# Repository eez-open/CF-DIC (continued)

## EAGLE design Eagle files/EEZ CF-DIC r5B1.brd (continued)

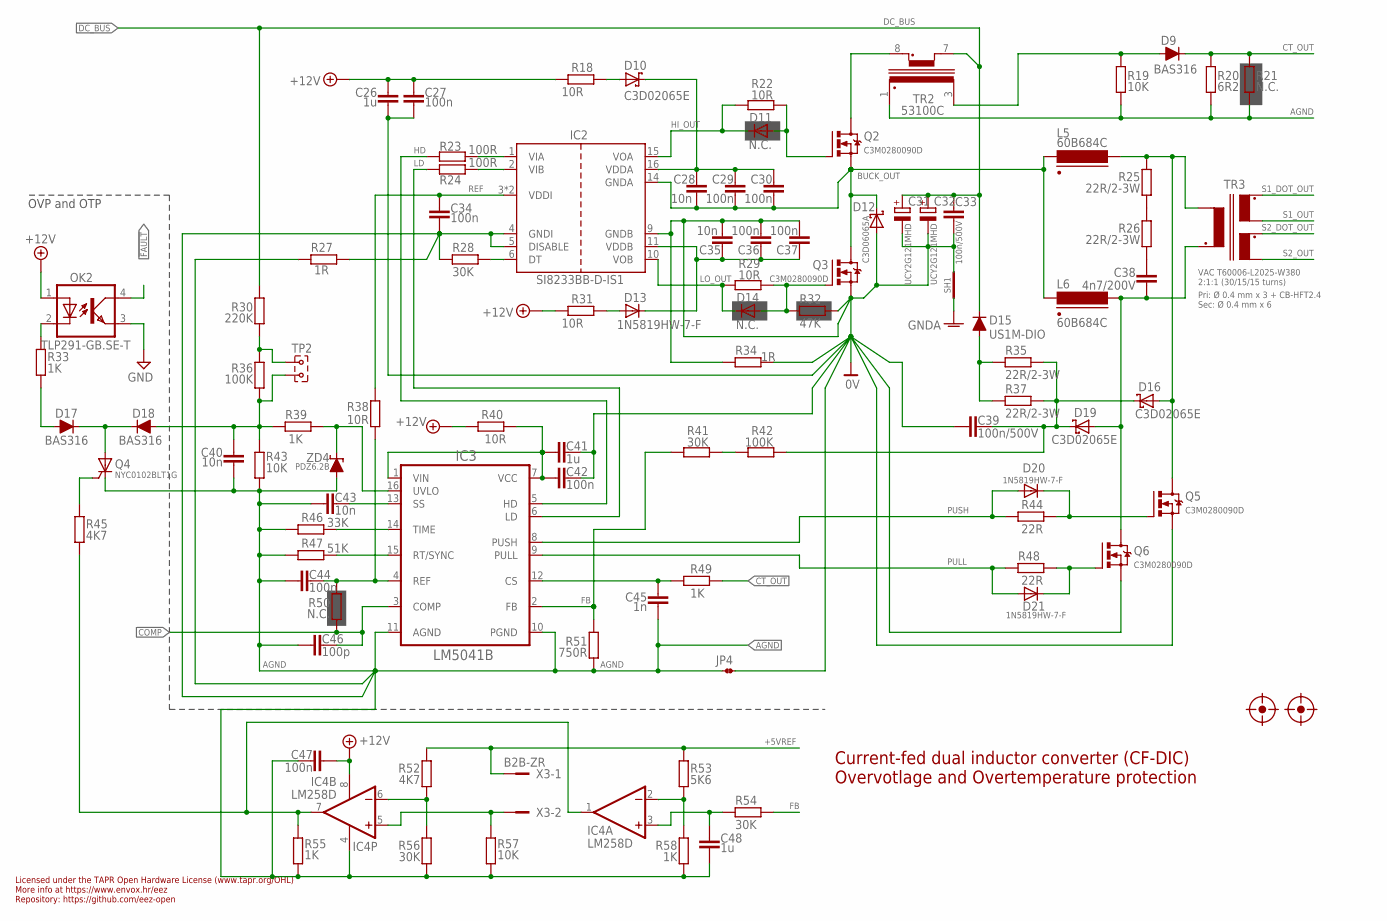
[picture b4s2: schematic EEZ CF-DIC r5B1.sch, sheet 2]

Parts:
C26, C41, C48: 1u; C0805
C27, C29, C30, C34, C36, C37, C42, C44, C47: 100n; C0603
C28, C35: 10n; C0603
C31, C32: UCY2G121MHD; ECAP7.5/18
C33, C39: 100n/500V; C1812
C38: 4n7/200V; C1210
C40, C43: 10n; C0805
C45: 1n; C0805
C46: 100p; C0805
D9, D17, D18: BAS316; SOD323-R
D10, D16, D19: C3D02065E; TO252
D11, D14: N.C.; SOD323-W
D12: C3D06065A; TO220-2
D13, D20, D21: 1N5819HW-7-F; SOD323-W
D15: US1M-DIO; DO214AA
FM1, FM2: FIDUCIAL_2; FIDUCIAL_DUAL
IC2: SI8233BB-D-IS1; SOIC-16
IC3: LM5041B; MTC16
IC4: LM258D; SOIC127P600X173-8N
JP4: JP2-NOCUT
L5, L6: 60B684C; MURATA_6000B
OK2: TLP291-GB.SE-T; SO4
Q2, Q3, Q5, Q6: C3M0280090D; TO247BV
Q4: NYC0102BLT1G; SOT23
R18, R22, R29, R31, R38, R40: 10R; R0805
R19, R43, R57: 10K; R0805
R20: 6R2; R0805
R21, R50: N.C.; R0805
R23, R24: 100R; R0805
R25, R26, R35, R37: 22R/2-3W; R2512
R27, R34: 1R; R0805
R28, R41, R54, R56: 30K; R0805
R30: 220K; R1206
R32: 47K; R0805
R33, R39, R49, R55, R58: 1K; R0805
R36, R42: 100K; R0805
R44, R48: 22R; R0805
R45, R52: 4K7; R0805
R46: 33K; R0805
R47: 51K; R0805
R51: 750R; R0805
R53: 5K6; R0805
SH1: SHORTNOHOLE; SHORT_NOHOLE
TP2: JUMPER-2PIN-2MM; 2MM-2
TR2: 53100C; MURATA_5300
TR3: VAC T60006-L2025-W380; VAC_DUAL_SEC
X3: B2B-ZR
ZD4: PDZ6.2B; SOD323-W

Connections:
0V: C26.1, C27.1, C31.-, C32.-, C33.2, C35.2, C36.2, C37.2, C39.1, C41.2, C42.2, D12.2 (A), IC2.9 (GNDB), JP4.2, Q3.S, Q5.S, Q6.S, R32.2, R34.1, R34.2, SH1.P$2 (GND_B); also elsewhere on the board
!FAULT: OK2.4 (COL); also elsewhere on the board
+5VREF: R52.2, R53.2, X3.1
+12V: C26.2, C27.2, C47.1, IC4.8 (V+), OK2.1 (A), R18.2, R31.2, R40.2; also elsewhere on the board
AGND: C34.1, C40.2, C43.1, C44.1, C45.1, C46.1, C47.2, C48.1, IC2.4 (GNDI), IC2.5 (DISABLE), IC3.10 (PGND), IC3.11 (AGND), IC4.4 (V-), JP4.1, Q4.1 (C), R19.2, R20.2, R21.2, R27.1, R27.2, R28.1, R43.2, R46.2, R47.2, R51.2, R55.2, R56.2, R57.2, R58.2, TR2.1 (S_DOT), ZD4.A; also elsewhere on the board
BUCK_OUT: C28.2, C29.2, C30.2, D12.1 (C), IC2.14 (GNDA), L5.2, L6.2, Q2.S, Q3.D
CLAMP_C: C39.2, D16.1 (C), D16.3 (C), D19.1 (C), D19.3 (C), R35.1, R37.1, R42.2
COMP: C46.2, IC3.3 (COMP), R50.2; also elsewhere on the board
CT_OUT: D9.C, R20.1, R21.1, R49.1
DC_BUS: C31.+, C32.+, C33.1, D15.C, R30.1, TR2.7; also elsewhere on the board
FB: IC3.2 (FB), R41.1, R51.1, R54.1
GND: OK2.3 (EMIT); also elsewhere on the board
GNDA: SH1.P$1 (GND_A); also elsewhere on the board
HD: IC3.5 (HD), R23.2
HI_OUT: D11.C, IC2.15 (VOA), R22.2
LD: IC3.6 (LD), R24.2
LO_OUT: D14.C, IC2.10 (VOB), R29.1
L_PULL: C38.2, D19.2 (A), L6.1, Q6.D, TR3.P1_DOT (P_DOT)
L_PUSH: D16.2 (A), L5.1, Q5.D, R25.2, TR3.P1
unnamed: R30.2, R36.1, TP2.1
unnamed: C28.1, C29.1, C30.1, D10.1 (C), D10.3 (C), IC2.16 (VDDA)
unnamed: R25.1, R26.2
unnamed: IC4.2 (-IN), R53.1, R58.1
unnamed: D20.C, Q5.G, R44.1
unnamed: D21.C, Q6.G, R48.1
unnamed: Q2.D, TR2.8 (P_DOT)
unnamed: C38.1, R26.1
unnamed: IC3.15 (RT/SYNC), R47.1
unnamed: D11.A, Q2.G, R22.1
unnamed: IC3.14 (TIME), R46.1
unnamed: C43.2, IC3.13 (SS)
unnamed: IC3.16 (UVLO), R39.1, ZD4.C
unnamed: IC4.6 (-IN), R52.1, R56.1
unnamed: D14.A, Q3.G, R29.2, R32.1
unnamed: R41.2, R42.1
unnamed: D10.2 (A), R18.1
unnamed: OK2.2 (C), R33.1
unnamed: C48.2, IC4.3 (+IN), R54.2
unnamed: D15.A, R35.2, R37.2
unnamed: IC2.1 (VIA), R23.1
unnamed: C45.2, IC3.12 (CS), R49.2
unnamed: IC4.1 (OUT), IC4.7 (OUT), R45.2, R55.1
unnamed: IC2.2 (VIB), R24.1
unnamed: IC4.5 (+IN), R57.1, X3.2
unnamed: IC2.6 (DT), R28.2
unnamed: D9.A, R19.1, TR2.3 (S)
unnamed: C41.1, C42.1, IC3.1 (VIN), IC3.7 (VCC), R40.1
unnamed: C35.1, C36.1, C37.1, D13.C, IC2.11 (VDDB)
unnamed: D13.A, R31.1
unnamed: C44.2, IC3.4 (REF), R38.1, R50.1
unnamed: Q4.2 (G), R45.1
unnamed: D17.C, D18.C, Q4.3 (A)
unnamed: D17.A, R33.2
PULL: D21.A, IC3.9 (PULL), R48.2
PUSH: D20.A, IC3.8 (PUSH), R44.2
REF: C34.2, IC2.3 (VDDI), IC2.8 (VDDI), R38.2
S1_DOT_OUT: TR3.S1_DOT; also elsewhere on the board
S1_OUT: TR3.S1; also elsewhere on the board
S2_DOT_OUT: TR3.S2_DOT; also elsewhere on the board
S2_OUT: TR3.S2; also elsewhere on the board
ULVO: C40.1, D18.A, R36.2, R39.2, R43.1, TP2.2

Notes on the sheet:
Licensed under the TAPR Open Hardware License (www.tapr.org/OHL)
Repository: https://github.com/eez-open
More info at https://www.envox.hr/eez
Current-fed dual inductor converter (CF-DIC) Overvotlage and Overtemperature protection
OVP and OTP
2:1:1 (30/15/15 turns)
Pri: Ø 0.4 mm x 3 + CB-HFT2.4
Sec: Ø 0.4 mm x 6

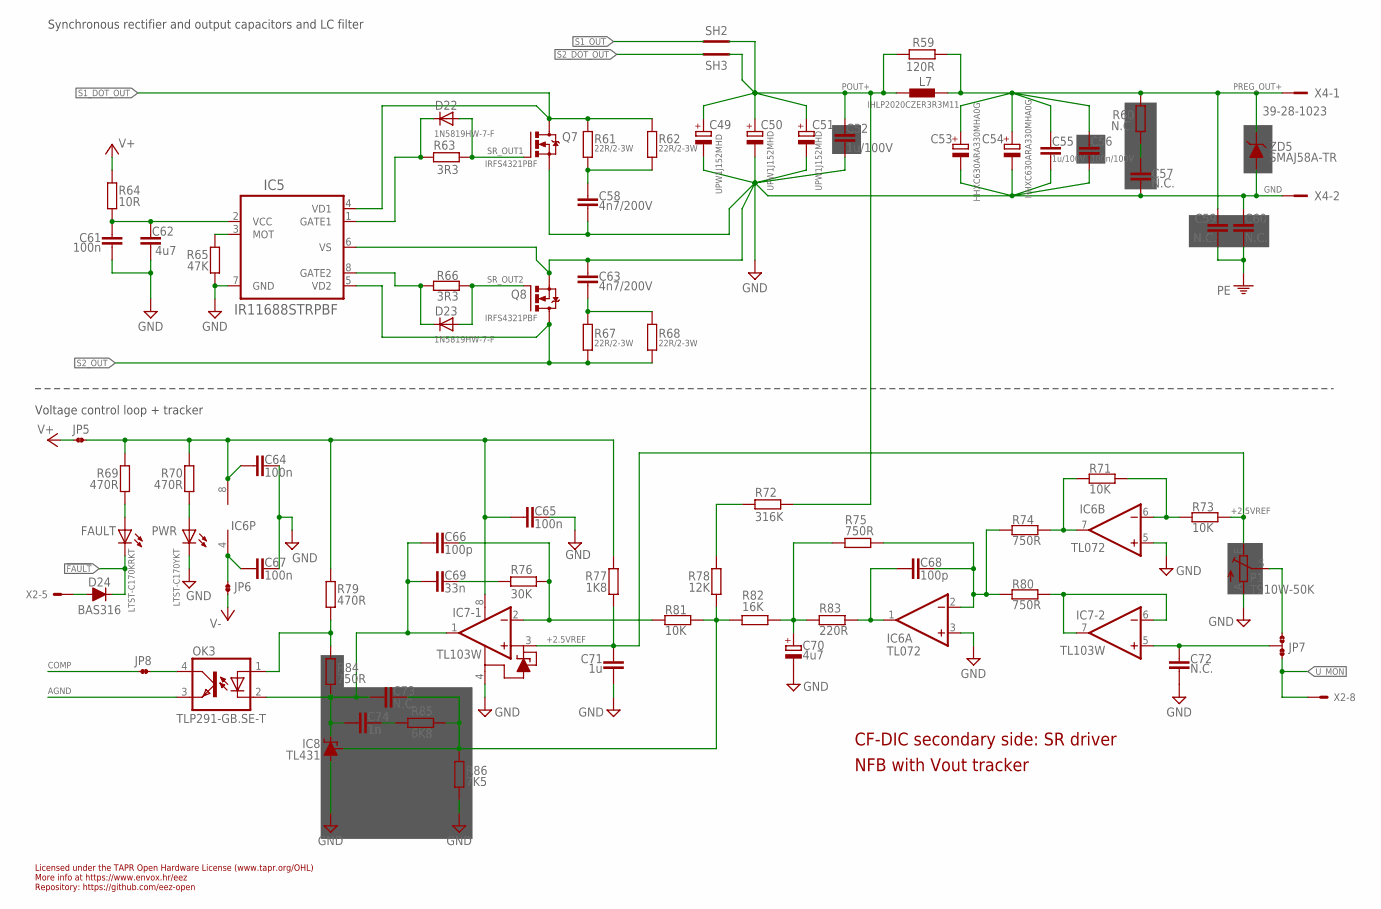
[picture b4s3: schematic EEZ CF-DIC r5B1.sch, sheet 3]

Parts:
C49, C50, C51: UPW1J152MHD; ECAP7.5/18
C52, C55: 1u/100V; C1206
C53: HHXC630ARA330MHA0G; CAPAE830X1050N; TOLERANCE ±20 %; VOLTAGERATING 63 V; MPN EEE-FK1J470P
C54: HHXC630ARA330MHA0G; CAPAE830X1050N
C56: 100n/100V; C1206
C57, C59, C60: N.C.; C1206
C58, C63: 4n7/200V; C1206
C61, C64, C65, C67: 100n; C0603
C62: 4u7; C1206
C66, C68: 100p; C0805
C69: 33n; C0805
C70: 4u7; EC1206
C71: 1u; C0805
C72, C73: N.C.; C0805
C74: 1n; C0805
D22, D23: 1N5819HW-7-F; SOD323-W
D24: BAS316; SOD323-R
FAULT: LTST-C170KRKT; LED_0805
IC5: IR11688STRPBF; SO8
IC6: TL072; SOIC127P600X173-8N
IC7: TL103W; SOIC127P600X173-8N
IC8: TL431; SOT103P240X110-3N
JP5, JP6, JP8: JP2-NOCUT
JP7: JP3-CUT
L7: IHLP2020CZER3R3M11; IHLP-2020BZ-11
OK3: TLP291-GB.SE-T; SO4
P1: T910W-50K; S64W
PWR: LTST-C170YKT; LED_0805
Q7, Q8: IRFS4321PBF; TO263
R59: 120R; R0805
R60: N.C.; R1210
R61, R62, R67, R68: 22R/2-3W; R2512
R63, R66: 3R3; R0805
R64: 10R; R0805
R65: 47K; R0805
R69, R70, R79: 470R; R0805
R71, R73, R81: 10K; R0805
R72: 316K; R0805
R74, R75, R80, R84: 750R; R0805
R76: 30K; R0805
R77: 1K8; R0805
R78: 12K; R0805
R82: 16K; R0805
R83: 220R; R0805
R85: 6K8; R0805
R86: 7K5; R0805
SH2, SH3: SHORTNOHOLE; SHORT_NOHOLE
X2: 90136-1208; 70543-08
X4: 39-28-1023; MINIFIT_5566-02A
ZD5: SMAJ58A-TR; DO214AC

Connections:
!FAULT: D24.C, FAULT.C; also elsewhere on the board
+2.5VREF: C71.1, IC7.3 (+IN1), P1.E, R73.2, R77.1
AGND: OK3.3 (EMIT); also elsewhere on the board
COMP: JP8.1; also elsewhere on the board
GND: C49.-, C50.-, C51.-, C52.2, C53.2, C54.2, C55.2, C56.2, C57.1, C58.2, C60.1, C61.2, C62.2, C63.2, C64.2, C65.2, C67.2, C70.-, C71.2, C72.2, IC5.6 (VS), IC5.7 (GND), IC6.3 (+IN), IC6.5 (+IN), IC7.4 (VCC-), IC8.3 (A), P1.A, PWR.C, Q7.2 (S), Q8.2 (S), R65.2, R86.1, X4.2, ZD5.A; also elsewhere on the board
unnamed: D24.A, X2.5
unnamed: C61.1, C62.1, IC5.2 (VCC), R64.2
unnamed: C57.2, R60.1
unnamed: C69.2, R76.2
unnamed: C66.2, IC7.2 (-IN1), R76.1, R81.1
unnamed: PWR.A, R70.2
unnamed: R72.1, R78.2
unnamed: FAULT.A, R69.2
unnamed: IC5.3 (MOT), R65.1
unnamed: C67.1, IC6.4 (V-), JP6.1
unnamed: JP8.2, OK3.4 (COL)
unnamed: C74.2, R85.1
unnamed: C64.1, C65.1, IC6.8 (V+), IC7.8 (VCC+), JP5.2, R69.1, R70.1, R77.2, R79.2
unnamed: IC6.7 (OUT), R71.1, R74.2
unnamed: C72.1, IC7.5 (+IN), JP7.COM
unnamed: JP7.NO, P1.S
unnamed: C68.2, IC6.2 (-IN), R74.1, R75.2, R80.1
unnamed: C58.1, R61.2, R62.2
unnamed: C63.1, R67.2, R68.2
unnamed: D22.C, IC5.1 (GATE1), R63.2
unnamed: D23.C, IC5.8 (GATE2), R66.2
unnamed: C66.1, C69.1, C73.1, C74.1, IC7.1 (OUT1), IC8.1 (C), OK3.2 (C), R84.2
unnamed: IC6.6 (-IN), R71.2, R73.1
unnamed: C68.1, IC6.1 (OUT), R83.2
NFB_IN: C73.2, IC8.2 (REF), R78.1, R81.2, R82.2, R85.2, R86.2
NFB_OFFSET: C70.+, R75.1, R82.1, R83.1
OK_A: OK3.1 (A), R79.1, R84.1
PE: C59.2, C60.2; also elsewhere on the board
POUT+: C49.+, C50.+, C51.+, C52.1, L7.1, R59.1, R72.2, SH2.P$2 (GND_B), SH3.P$1 (GND_A)
PREG_OUT+: C53.1, C54.1, C55.1, C56.1, C59.1, L7.2, R59.2, R60.2, X4.1, ZD5.C; also elsewhere on the board
S1_DOT_OUT: IC5.4 (VD1), Q7.3 (D), R61.1, R62.1; also elsewhere on the board
S1_OUT: SH2.P$1 (GND_A); also elsewhere on the board
S2_DOT_OUT: SH3.P$2 (GND_B); also elsewhere on the board
S2_OUT: IC5.5 (VD2), Q8.3 (D), R67.1, R68.1; also elsewhere on the board
SR_OUT1: D22.A, Q7.1 (G), R63.1
SR_OUT2: D23.A, Q8.1 (G), R66.1
U_MON: JP7.NC, X2.8
U_MON1: IC7.6 (-IN), IC7.7 (OUT), R80.2
V+: JP5.1, R64.1; also elsewhere on the board
V-: JP6.2; also elsewhere on the board

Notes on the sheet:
Licensed under the TAPR Open Hardware License (www.tapr.org/OHL)
Repository: https://github.com/eez-open
More info at https://www.envox.hr/eez
CF-DIC secondary side: SR driver
NFB with Vout tracker
Voltage control loop + tracker
Synchronous rectifier and output capacitors and LC filter

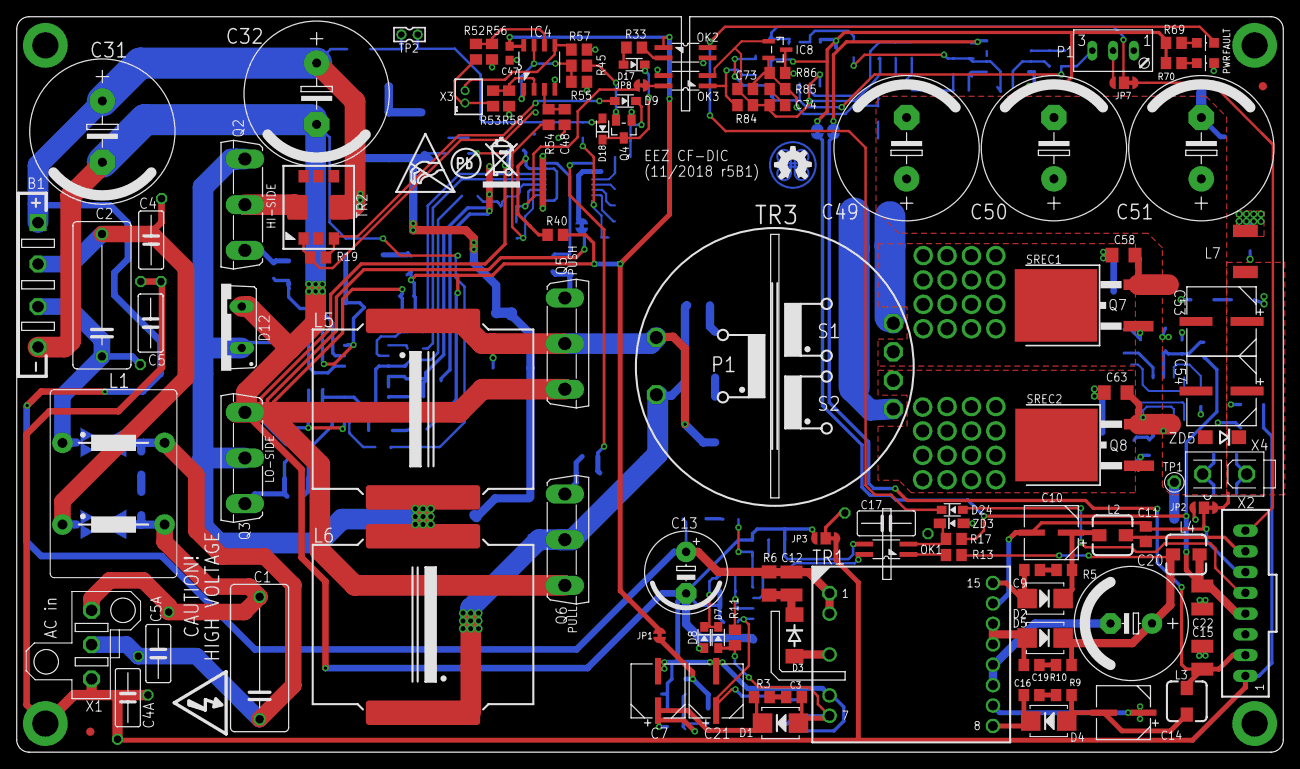
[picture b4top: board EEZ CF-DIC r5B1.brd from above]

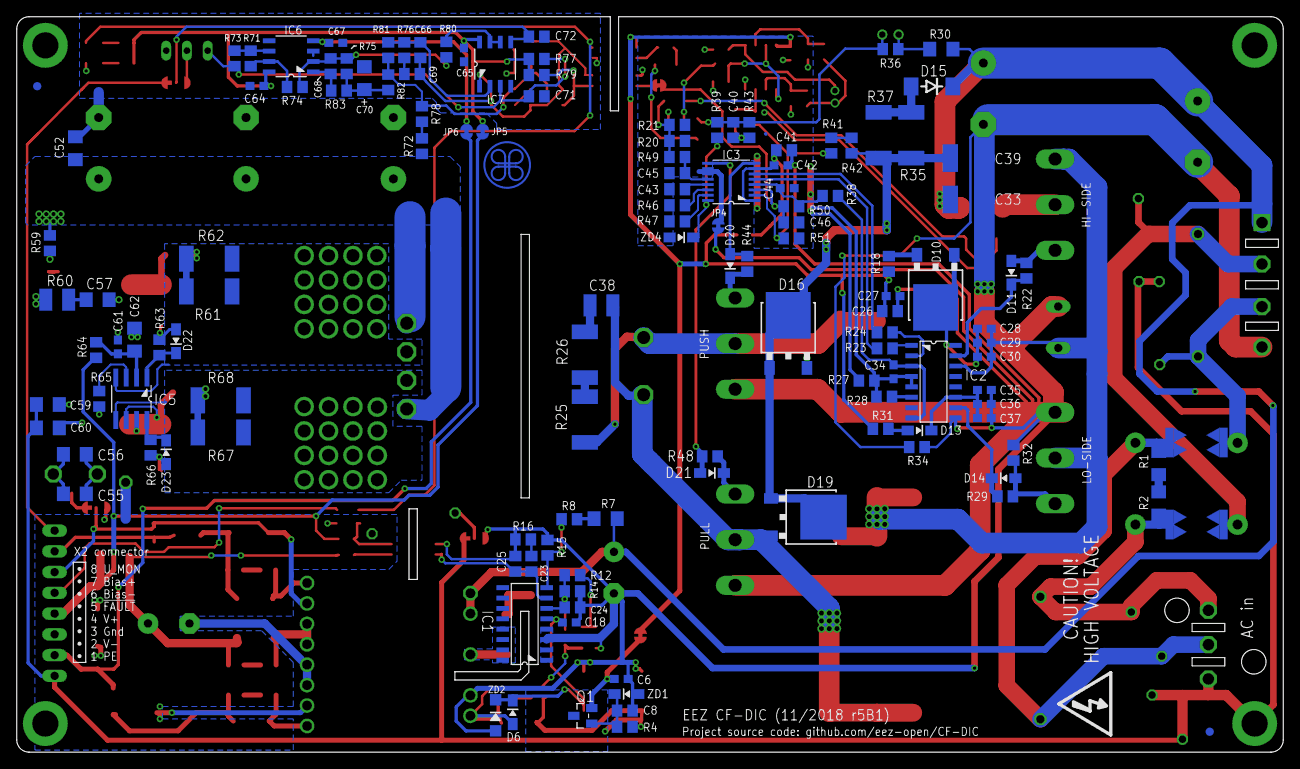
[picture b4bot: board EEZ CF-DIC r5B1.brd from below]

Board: 2 copper layers, 155.0 x 90.0 mm, 249 parts (132 on the bottom side), 131 nets.

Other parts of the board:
EEZ_SIGNATURE: SIGNATURESMALL; SIGNATURE_5MM
U$2: RECYCLE_BIN1/8
U$4: ESD_SYMBOL
U$5: PB_SMALL

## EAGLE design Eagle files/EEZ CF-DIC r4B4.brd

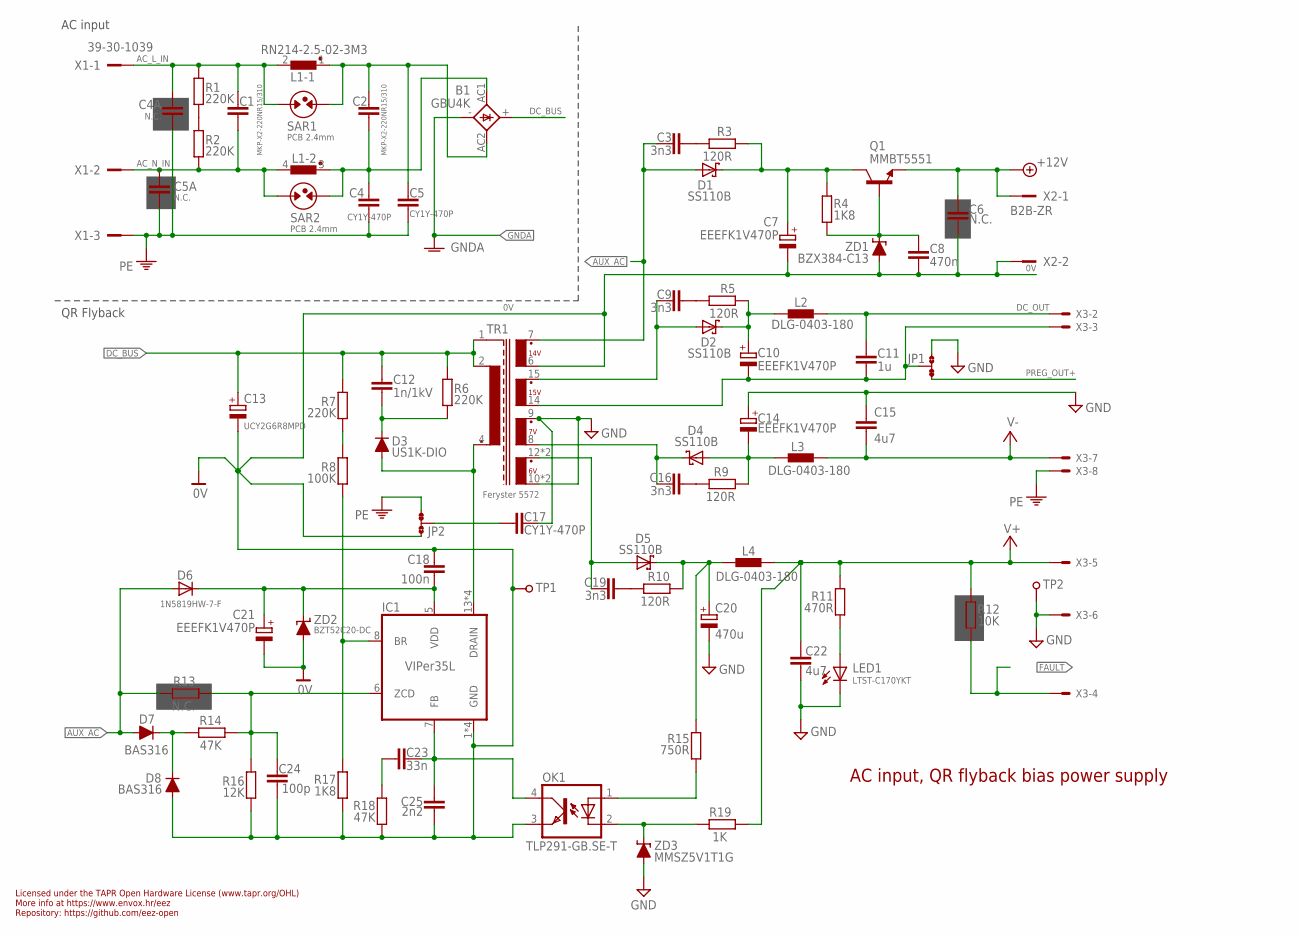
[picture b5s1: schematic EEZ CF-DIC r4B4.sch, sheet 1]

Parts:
B1: GBU4K; GBU4K_CRE
C1, C2: MKP-X2-220NR15/310; C150-072X183
C3, C9, C16, C19: 3n3; C0805
C4, C5, C17: CY1Y-470P; CY075-032X103
C4A, C5A: N.C.; CY075-032X103
C6: N.C.; C0603
C7, C10, C14, C21: EEEFK1V470P; CAPAE660X610N
C8: 470n; C0805
C11: 1u; C0805
C12: 1n/1kV; C1210
C13: UCY2G6R8MPD; ECAP5/10.5
C15, C22: 4u7; C1206
C18: 100n; C0603
C20: 470u; ECAP5/10.5
C23: 33n; C0805
C24: 100p; C0805
C25: 2n2; C0805
D1, D2, D4, D5: SS110B; SMB
D3: US1K-DIO; DO214AA
D6: 1N5819HW-7-F; SOD323-W
D7, D8: BAS316; SOD323-R
IC1: VIPer35L; SOIC-16
JP1, JP2: JP3-CUT
L1: RN214-2.5-02-3M3; RN214; FARNELL 1191518
L2, L3, L4: DLG-0403-180; DE0403
LED1: LTST-C170YKT; LED_0805
OK1: TLP291-GB.SE-T; SO4
Q1: MMBT5551; SOT23-BEC
R1, R2, R6, R7: 220K; R1206
R3, R5, R9, R10: 120R; R0805
R4, R17: 1K8; R0805
R8: 100K; R0805
R11: 470R; R0805
R12: 10K; R0805
R13: N.C.; R0805
R14, R18: 47K; R0805
R15: 750R; R0805
R16: 12K; R0805
R19: 1K; R0805
SAR1, SAR2: PCB 2.4mm; PCB-SAR_2.4MM
TP1, TP2: PCB_TEST_TABSHIELD; PCB_SHIELD_TAB
TR1: Feryster 5572; FERYSTER_5572
X1: 39-30-1039; MINIFIT_39301039_CRE
X2: B2B-ZR
X3: 90136-1208; 70543-08
ZD1: BZX384-C13; SOD323-W
ZD2: BZT52C20-DC; SOD123
ZD3: MMSZ5V1T1G; SOD323-W

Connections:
0V: C6.2, C7.2 (-), C8.2, C13.-, C18.1, C21.2 (-), C24.2, C25.2, D8.A, IC1.1 (GND), IC1.2 (GND), IC1.3 (GND), IC1.4 (GND), JP2.NO, OK1.3 (EMIT), R16.1, R17.2, R18.2, TP1.1, TR1.6 (S_BIAS), X2.2, ZD1.A, ZD2.A; also elsewhere on the board
6VAC: C19.2, D5.A, TR1.12 (S1_DOT), TR1.13 (S1_DOT)
7VAC: C16.2, D4.C, TR1.8 (S2)
15VAC: C9.2, D2.A, TR1.15 (S3_DOT)
!FAULT: R12.2, X3.4; also elsewhere on the board
+6V_REC: C20.+, D5.C, L4.1, R10.1, R15.1
+12V: C6.1, Q1.E, X2.1; also elsewhere on the board
+15V_REC: C10.1 (+), D2.C, L2.1, R5.1
-7V_REC: C14.2 (-), D4.A, L3.1, R9.1
-15V: C10.2 (-), C11.2, JP1.COM, TR1.14 (S3), X3.3
AC_L_IN: C1.1, C4A.2, L1.2, R1.1, SAR1.1, X1.1
AC_N_IN: C1.2, C5A.2, L1.4 (2), R2.2, SAR2.1, X1.2
AUX_AC: C3.2, D1.A, D6.A, D7.A, R13.2, TR1.7 (S_BIAS_DOT)
AUX_REC: C7.1 (+), D1.C, Q1.C, R3.1, R4.1
DC_BUS: B1.+, C12.1, C13.+, R6.1, R7.1, TR1.1 (SHIELD), TR1.2; also elsewhere on the board
DC_OUT: C11.1, L2.2, X3.2
FB2: OK1.2 (C), R19.1, ZD3.C
GND: C14.1 (+), C15.1, C17.2, C20.-, C22.2, JP1.NO, LED1.C, TP2.1, TR1.9 (S2_DOT), TR1.10 (S1), TR1.11 (S1), X3.6, ZD3.A; also elsewhere on the board
GNDA: B1.-; also elsewhere on the board
unnamed: C17.1, JP2.COM
unnamed: LED1.A, R11.2
unnamed: B1.AC2, C2.1, C5.2, L1.1, SAR1.2
unnamed: IC1.8 (BR), R8.2, R17.1
unnamed: B1.AC1, C2.2, C4.2, L1.3 (1), SAR2.2
unnamed: C18.2, C21.1 (+), D6.C, IC1.5 (VDD), ZD2.C
unnamed: R1.2, R2.1
unnamed: R7.2, R8.1
unnamed: C8.1, Q1.B, R4.2, ZD1.C
unnamed: OK1.1 (A), R15.2
unnamed: C12.2, D3.C, R6.2
unnamed: C23.2, C25.1, IC1.7 (FB), OK1.4 (COL)
unnamed: C9.1, R5.2
unnamed: C3.1, R3.2
unnamed: C24.1, IC1.6 (ZCD), R13.1, R14.1, R16.2
unnamed: C16.1, R9.2
unnamed: C19.1, R10.2
unnamed: C23.1, R18.1
unnamed: D7.C, D8.C, R14.2
PE: C4.1, C4A.1, C5.1, C5A.1, JP2.NC, X1.3, X3.8
PREG_OUT+: JP1.NC; also elsewhere on the board
V+: C22.1, L4.2, R11.1, R12.1, R19.2, X3.5; also elsewhere on the board
V-: C15.2, L3.2, X3.7; also elsewhere on the board
VIPER_D: D3.A, IC1.13 (DRAIN), IC1.14 (DRAIN), IC1.15 (DRAIN), IC1.16 (DRAIN), TR1.4 (P2_DOT)

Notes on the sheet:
Licensed under the TAPR Open Hardware License (www.tapr.org/OHL)
Repository: https://github.com/eez-open
More info at https://www.envox.hr/eez
AC input, QR flyback bias power supply
QR Flyback
AC input

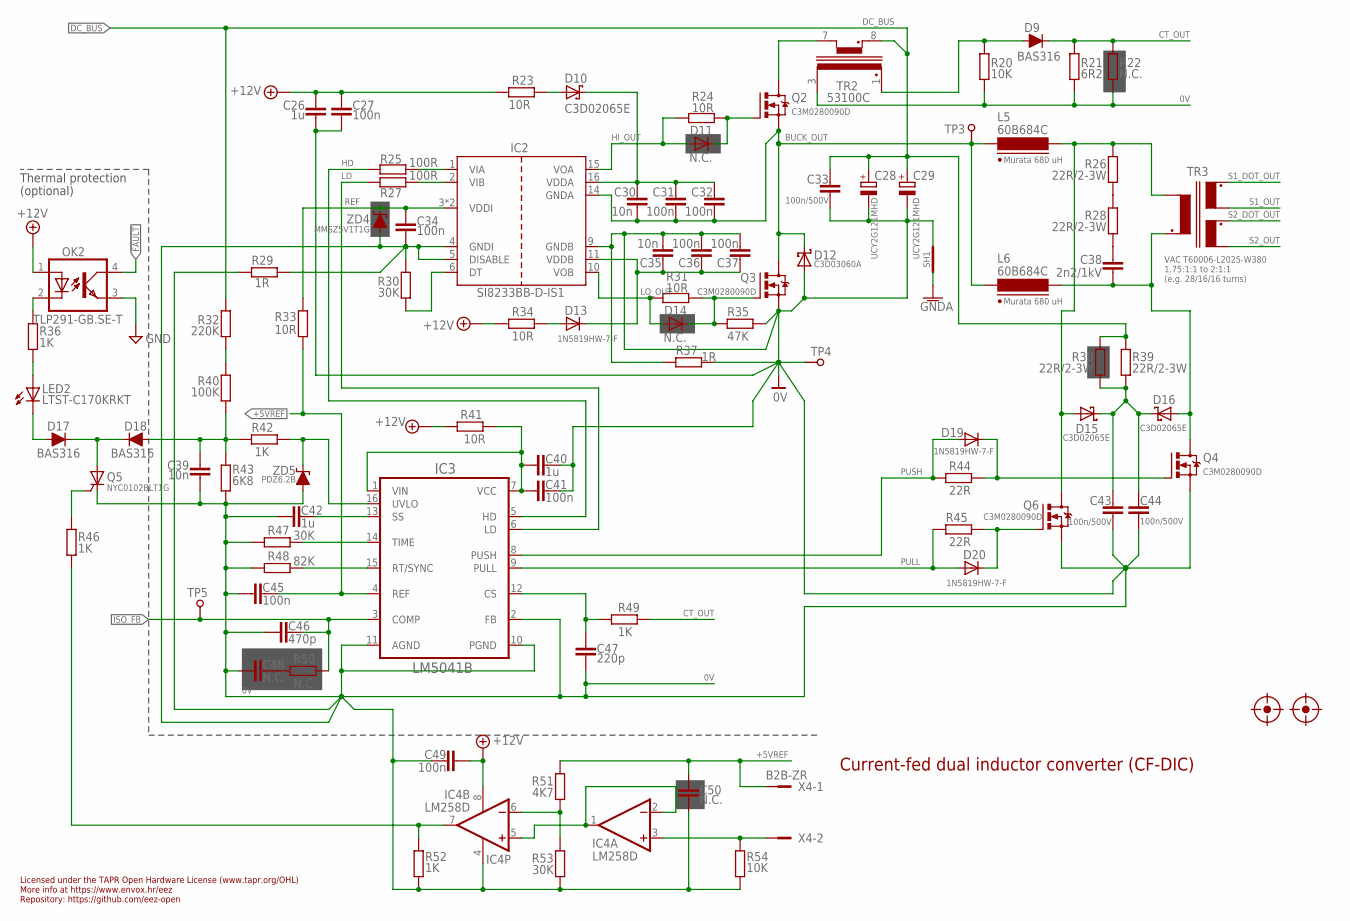
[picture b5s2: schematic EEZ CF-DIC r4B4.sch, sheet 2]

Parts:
C26, C40, C42: 1u; C0805
C27, C31, C32, C34, C36, C37, C41, C45, C49: 100n; C0603
C28, C29: UCY2G121MHD; ECAP7.5/18
C30, C35, C39: 10n; C0603
C33, C43, C44: 100n/500V; C1812
C38: 2n2/1kV; C1210
C46: 470p; C0805
C47: 220p; C0805
C48: N.C.; C0805
C50: N.C.; C0603
D9, D17, D18: BAS316; SOD323-R
D10, D15, D16: C3D02065E; TO252
D11, D14: N.C.; SOD323-W
D12: C3D03060A; TO220-2
D13, D19, D20: 1N5819HW-7-F; SOD323-W
FM1, FM2: FIDUCIAL_2; FIDUCIAL_DUAL
IC2: SI8233BB-D-IS1; SOIC-16
IC3: LM5041B; MTC16
IC4: LM258D; SOIC127P600X173-8N
L5, L6: 60B684C; MURATA_6000B
LED2: LTST-C170KRKT; LED_0805
OK2: TLP291-GB.SE-T; SO4
Q2, Q3, Q4, Q6: C3M0280090D; TO247BV-ROUND
Q5: NYC0102BLT1G; SOT23
R20, R54: 10K; R0805
R21: 6R2; R0805
R22, R50: N.C.; R0805
R23, R24, R31, R33, R34, R41: 10R; R0805
R25, R27: 100R; R0805
R26, R28, R38, R39: 22R/2-3W; R2512
R29, R37: 1R; R0805
R30, R47, R53: 30K; R0805
R32: 220K; R1206
R35: 47K; R0805
R36, R42, R46, R49, R52: 1K; R0805
R40: 100K; R0805
R43: 6K8; R0805
R44, R45: 22R; R0805
R48: 82K; R0805
R51: 4K7; R0805
SH1: SHORTNOHOLE; SHORT_NOHOLE
TP3, TP4, TP5: PCB_TEST_TABSHIELD; PCB_SHIELD_TAB
TR2: 53100C; MURATA_5300
TR3: VAC T60006-L2025-W380; VAC_DUAL_SEC
X4: B2B-ZR
ZD4: MMSZ5V1T1G; SOD323-W
ZD5: PDZ6.2B; SOD323-W

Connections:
0V: C26.1, C27.1, C28.-, C29.-, C33.1, C34.1, C35.2, C36.2, C37.2, C39.2, C40.2, C41.2, C42.1, C43.1, C44.1, C45.1, C46.1, C47.1, C48.1, C49.2, C50.2, D12.2 (A), IC2.4 (GNDI), IC2.5 (DISABLE), IC2.9 (GNDB), IC3.2 (FB), IC3.10 (PGND), IC3.11 (AGND), IC4.4 (V-), Q3.S, Q4.S, Q5.1 (C), Q6.S, R20.2, R21.2, R22.2, R29.1, R29.2, R30.1, R35.2, R37.1, R37.2, R43.2, R47.2, R48.2, R52.2, R53.2, R54.2, SH1.P$2 (GND_B), TP4.1, TR2.3 (S), ZD4.A, ZD5.A; also elsewhere on the board
!FAULT: OK2.4 (COL); also elsewhere on the board
+5VREF: C45.2, C50.1, IC3.4 (REF), R33.1, R51.2, X4.1
+12V: C26.2, C27.2, C49.1, IC4.8 (V+), OK2.1 (A), R23.2, R34.2, R41.2; also elsewhere on the board
BUCK_OUT: C30.2, C31.2, C32.2, D12.1 (C), IC2.14 (GNDA), L5.2, L6.2, Q2.S, Q3.D, TP3.1
CLAMP_C: C43.2, C44.2, D15.1 (C), D15.3 (C), D16.1 (C), D16.3 (C), R38.1, R39.1
CT_OUT: D9.C, R21.1, R22.1, R49.1
DC_BUS: C28.+, C29.+, C33.2, R32.1, R38.2, R39.2, TR2.8 (P_DOT); also elsewhere on the board
GND: OK2.3 (EMIT); also elsewhere on the board
GNDA: SH1.P$1 (GND_A); also elsewhere on the board
HD: IC3.5 (HD), R25.2
HI_OUT: D11.A, IC2.15 (VOA), R24.2
ISO_FB: C46.2, IC3.3 (COMP), R50.1, TP5.1; also elsewhere on the board
LD: IC3.6 (LD), R27.2
LO_OUT: D14.A, IC2.10 (VOB), R31.1
L_PULL: D15.2 (A), L5.1, Q6.D, R26.2, TR3.P1
L_PUSH: C38.2, D16.2 (A), L6.1, Q4.D, TR3.P1_DOT (P_DOT)
unnamed: R32.2, R40.1
unnamed: C30.1, C31.1, C32.1, D10.1 (C), D10.3 (C), IC2.16 (VDDA)
unnamed: R26.1, R28.2
unnamed: IC4.3 (+IN), R54.1, X4.2
unnamed: D19.C, Q4.G, R44.1
unnamed: D20.C, Q6.G, R45.1
unnamed: LED2.A, R36.2
unnamed: C38.1, R28.1
unnamed: IC3.15 (RT/SYNC), R48.1
unnamed: D11.C, Q2.G, R24.1
unnamed: IC3.14 (TIME), R47.1
unnamed: C42.2, IC3.13 (SS)
unnamed: IC3.16 (UVLO), R42.1, ZD5.C
unnamed: IC4.6 (-IN), R51.1, R53.1
unnamed: D14.C, Q3.G, R31.2, R35.1
unnamed: D10.2 (A), R23.1
unnamed: OK2.2 (C), R36.1
unnamed: C48.2, R50.2
unnamed: IC2.1 (VIA), R25.1
unnamed: C47.2, IC3.12 (CS), R49.2
unnamed: IC4.7 (OUT), R46.2, R52.1
unnamed: IC2.2 (VIB), R27.1
unnamed: IC4.1 (OUT), IC4.2 (-IN), IC4.5 (+IN)
unnamed: IC2.6 (DT), R30.2
unnamed: D9.A, R20.1, TR2.1 (S_DOT)
unnamed: C40.1, C41.1, IC3.1 (VIN), IC3.7 (VCC), R41.1
unnamed: C35.1, C36.1, C37.1, D13.C, IC2.11 (VDDB)
unnamed: Q2.D, TR2.7
unnamed: D13.A, R34.1
unnamed: Q5.2 (G), R46.1
unnamed: D17.C, D18.C, Q5.3 (A)
unnamed: D17.A, LED2.C
PULL: D20.A, IC3.9 (PULL), R45.2
PUSH: D19.A, IC3.8 (PUSH), R44.2
REF: C34.2, IC2.3 (VDDI), IC2.8 (VDDI), R33.2, ZD4.C
S1_DOT_OUT: TR3.S1_DOT; also elsewhere on the board
S1_OUT: TR3.S1; also elsewhere on the board
S2_DOT_OUT: TR3.S2_DOT; also elsewhere on the board
S2_OUT: TR3.S2; also elsewhere on the board
ULVO: C39.1, D18.A, R40.2, R42.2, R43.1

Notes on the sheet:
Licensed under the TAPR Open Hardware License (www.tapr.org/OHL)
Repository: https://github.com/eez-open
More info at https://www.envox.hr/eez
Current-fed dual inductor converter (CF-DIC)
1.75:1:1 to 2:1:1
Murata 680 uH
(e.g. 28/16/16 turns)
(optional)
Thermal protection

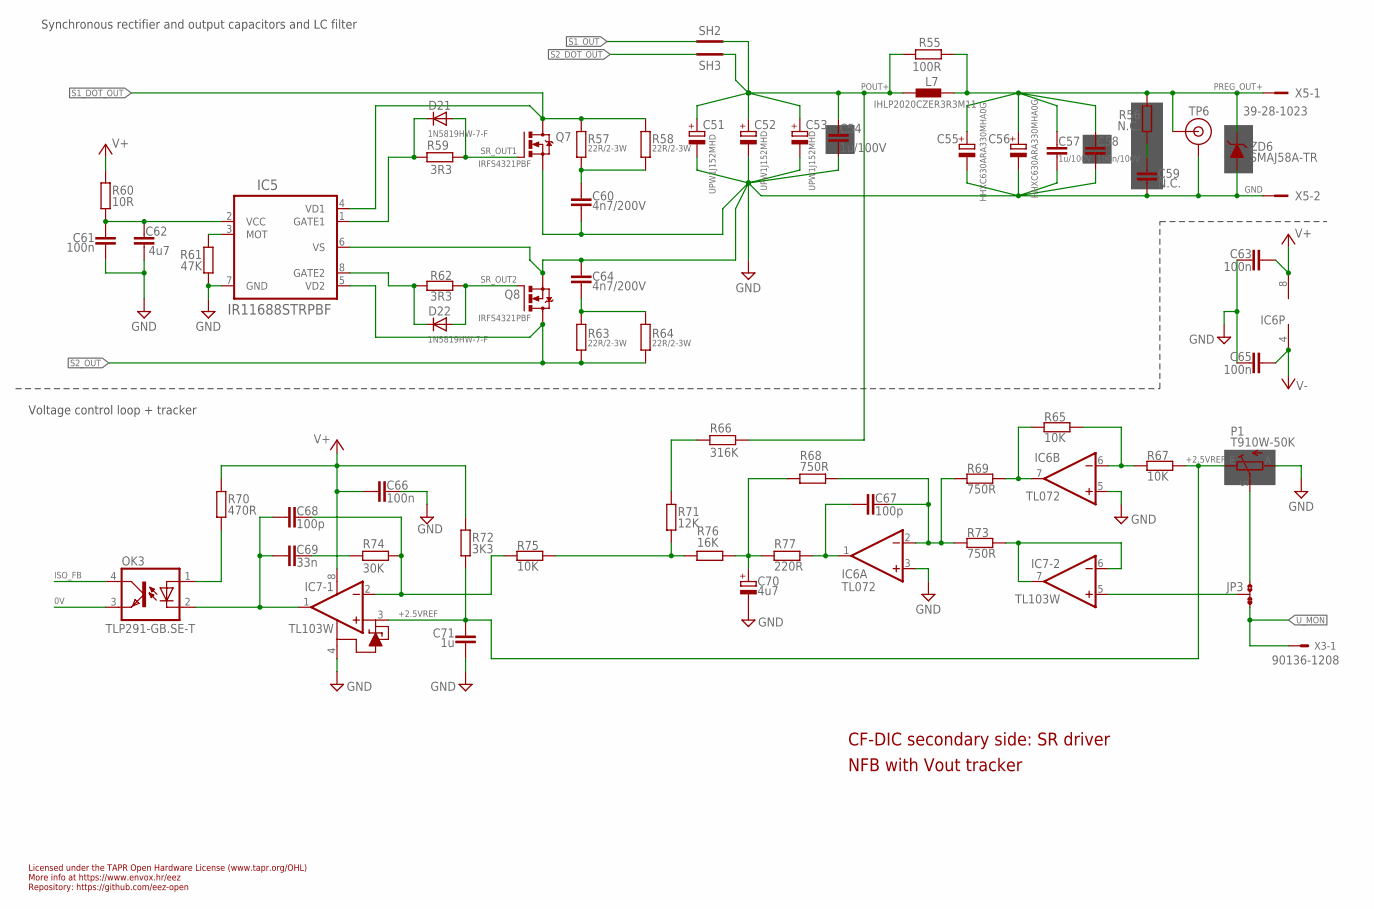
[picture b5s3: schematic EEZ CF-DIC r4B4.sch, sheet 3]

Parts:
C51, C52, C53: UPW1J152MHD; ECAP7.5/18
C54, C57: 1u/100V; C1206
C55: HHXC630ARA330MHA0G; CAPAE830X1050N; TOLERANCE ±20 %; VOLTAGERATING 63 V; MPN EEE-FK1J470P
C56: HHXC630ARA330MHA0G; CAPAE830X1050N
C58: 100n/100V; C0805
C59: N.C.; C1206
C60, C64: 4n7/200V; C1206
C61, C63, C65, C66: 100n; C0603
C62: 4u7; C1206
C67, C68: 100p; C0805
C69: 33n; C0805
C70: 4u7; EC1206
C71: 1u; C0805
D21, D22: 1N5819HW-7-F; SOD323-W
IC5: IR11688STRPBF; SO8
IC6: TL072; SOIC127P600X173-8N
IC7: TL103W; SOIC127P600X173-8N
JP3: JP3-CUT
L7: IHLP2020CZER3R3M11; IHLP-2020BZ-11
OK3: TLP291-GB.SE-T; SO4
P1: T910W-50K; S64W
Q7, Q8: IRFS4321PBF; TO263
R55: 100R; R0805
R56: N.C.; R1210
R57, R58, R63, R64: 22R/2-3W; R2512
R59, R62: 3R3; R0805
R60: 10R; R0805
R61: 47K; R0805
R65, R67, R75: 10K; R0805
R66: 316K; R0805
R68, R69, R73: 750R; R0805
R70: 470R; R0805
R71: 12K; R0805
R72: 3K3; R0805
R74: 30K; R0805
R76: 16K; R0805
R77: 220R; R0805
SH2, SH3: SHORTNOHOLE; SHORT_NOHOLE
TP6: TEST_POINT-2; TP_1.1MM_2
X3: 90136-1208; 70543-08
X5: 39-28-1023; MINIFIT_5566-02A
ZD6: SMAJ58A-TR; DO214AC

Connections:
0V: OK3.3 (EMIT); also elsewhere on the board
+2.5VREF: C71.1, IC7.3 (+IN1), P1.E, R67.2, R72.1
FB: R71.1, R75.2, R76.2
GND: C51.-, C52.-, C53.-, C54.2, C55.2, C56.2, C57.2, C58.2, C59.1, C60.2, C61.2, C62.2, C63.2, C64.2, C65.2, C66.2, C70.-, C71.2, IC5.6 (VS), IC5.7 (GND), IC6.3 (+IN), IC6.5 (+IN), IC7.4 (VCC-), P1.A, Q7.2 (S), Q8.2 (S), R61.2, TP6.GND, X5.2, ZD6.A; also elsewhere on the board
ISO_FB: OK3.4 (COL); also elsewhere on the board
unnamed: C61.1, C62.1, IC5.2 (VCC), R60.2
unnamed: C59.2, R56.1
unnamed: C69.2, R74.2
unnamed: C68.2, IC7.2 (-IN1), R74.1, R75.1
unnamed: R66.1, R71.2
unnamed: IC5.3 (MOT), R61.1
unnamed: IC6.7 (OUT), R65.1, R69.2
unnamed: IC7.5 (+IN), JP3.COM
unnamed: JP3.NO, P1.S
unnamed: C67.2, IC6.2 (-IN), R68.2, R69.1, R73.1
unnamed: C60.1, R57.2, R58.2
unnamed: C64.1, R63.2, R64.2
unnamed: D21.C, IC5.1 (GATE1), R59.2
unnamed: D22.C, IC5.8 (GATE2), R62.2
unnamed: C68.1, C69.1, IC7.1 (OUT1), OK3.2 (C)
unnamed: IC6.6 (-IN), R65.2, R67.1
unnamed: C67.1, IC6.1 (OUT), R77.2
NFB_OFFSET: C70.+, R68.1, R76.1, R77.1
OK_A: OK3.1 (A), R70.1
POUT+: C51.+, C52.+, C53.+, C54.1, L7.1, R55.1, R66.2, SH2.P$2 (GND_B), SH3.P$1 (GND_A)
PREG_OUT+: C55.1, C56.1, C57.1, C58.1, L7.2, R55.2, R56.2, TP6.TIP, X5.1, ZD6.C; also elsewhere on the board
S1_DOT_OUT: IC5.4 (VD1), Q7.3 (D), R57.1, R58.1; also elsewhere on the board
S1_OUT: SH2.P$1 (GND_A); also elsewhere on the board
S2_DOT_OUT: SH3.P$2 (GND_B); also elsewhere on the board
S2_OUT: IC5.5 (VD2), Q8.3 (D), R63.1, R64.1; also elsewhere on the board
SR_OUT1: D21.A, Q7.1 (G), R59.1
SR_OUT2: D22.A, Q8.1 (G), R62.1
U_MON: JP3.NC, X3.1
U_MON1: IC7.6 (-IN), IC7.7 (OUT), R73.2
V+: C63.1, C66.1, IC6.8 (V+), IC7.8 (VCC+), R60.1, R70.2, R72.2; also elsewhere on the board
V-: C65.1, IC6.4 (V-); also elsewhere on the board

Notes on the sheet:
Licensed under the TAPR Open Hardware License (www.tapr.org/OHL)
Repository: https://github.com/eez-open
More info at https://www.envox.hr/eez
CF-DIC secondary side: SR driver
NFB with Vout tracker
Voltage control loop + tracker
Synchronous rectifier and output capacitors and LC filter

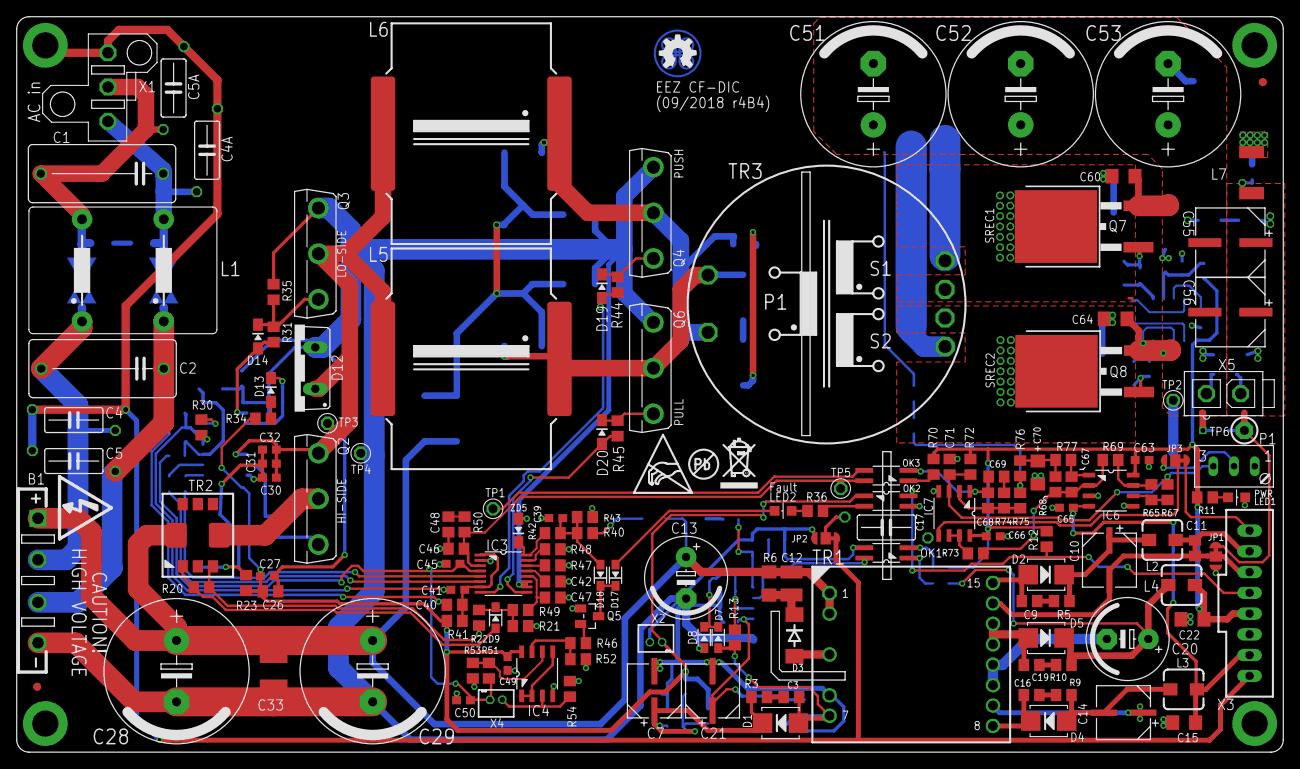
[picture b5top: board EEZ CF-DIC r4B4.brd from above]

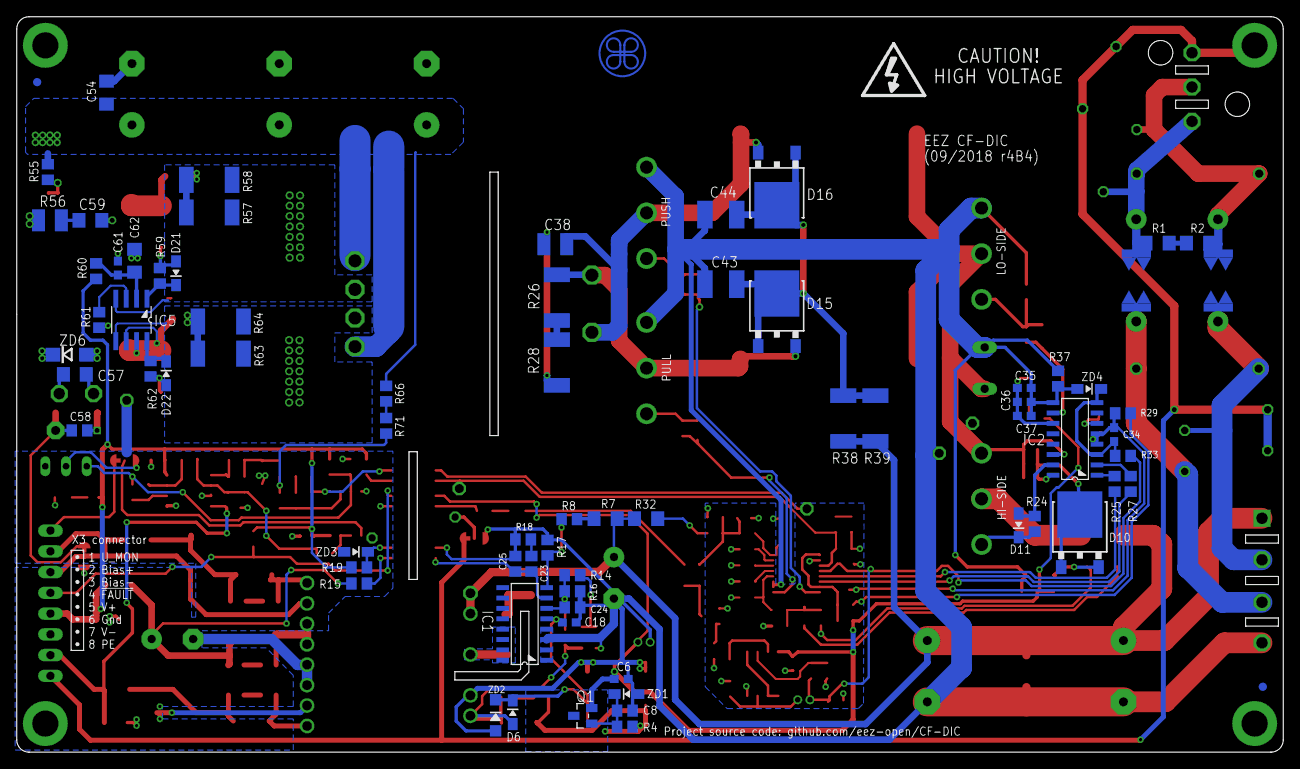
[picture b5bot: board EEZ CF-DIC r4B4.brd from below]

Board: 2 copper layers, 155.0 x 90.0 mm, 235 parts (72 on the bottom side), 120 nets.

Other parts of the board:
EEZ_SIGNATURE: SIGNATURESMALL; SIGNATURE_5MM
U$2: RECYCLE_BIN1/8
U$4: ESD_SYMBOL
U$5: PB_SMALL
